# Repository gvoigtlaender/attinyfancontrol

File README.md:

# attinyfancontrol
control USB fan with Attiny85 &amp; DS18B20 Sensor

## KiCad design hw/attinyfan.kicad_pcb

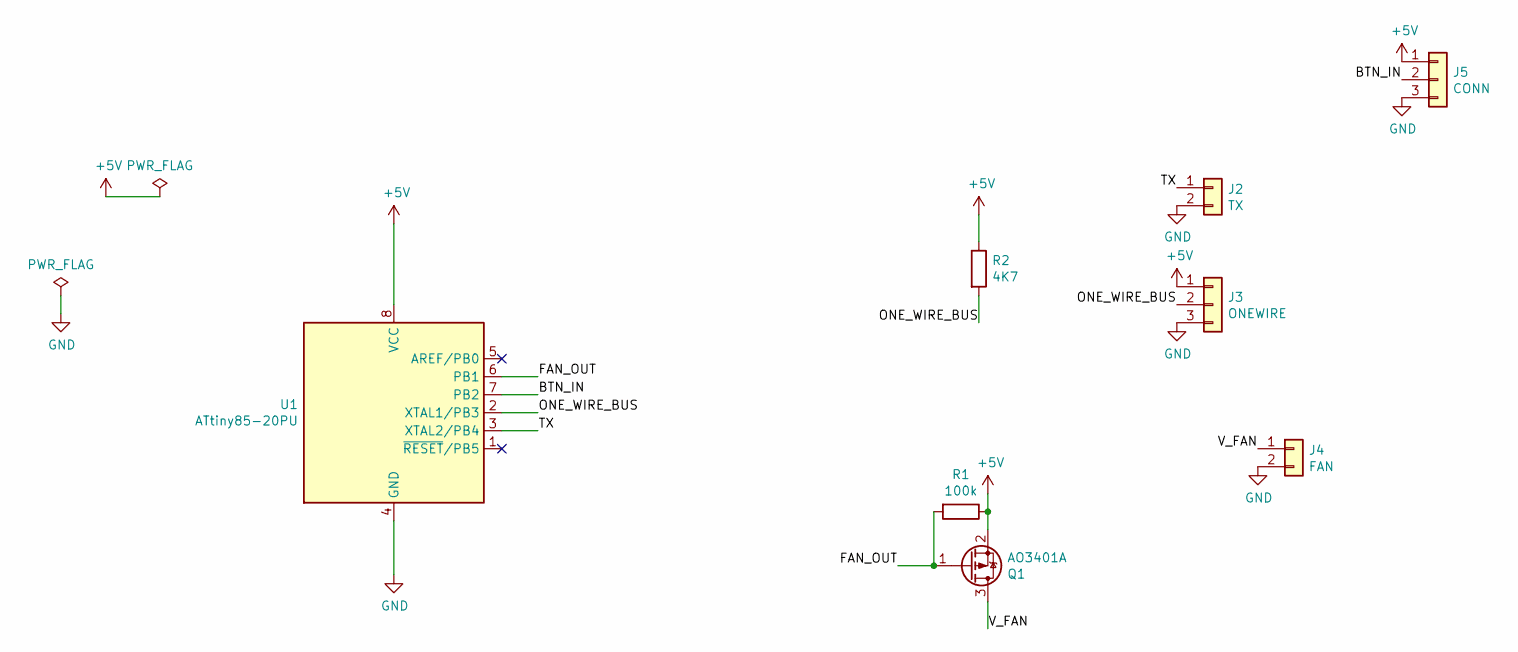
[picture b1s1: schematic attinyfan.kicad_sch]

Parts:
J2: TX; PinHeader_1x02_P2.54mm_Vertical
J3: ONEWIRE; PinHeader_1x03_P2.54mm_Vertical
J4: FAN; PinHeader_1x02_P2.54mm_Vertical
J5: CONN; PinHeader_1x03_P2.54mm_Vertical
Q1: AO3401A; SOT-23
R1: 100k; R_0805_2012Metric
R2: 4K7; R_0805_2012Metric
U1: ATtiny85-20PU; DIP-8_W7.62mm

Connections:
+5V: J3.1, J5.1, Q1.2 (S), R1.1, R2.1, U1.8 (VCC)
/BTN_IN: J5.2, U1.7 (PB2)
/FAN_OUT: Q1.1 (G), R1.2, U1.6 (PB1)
/ONE_WIRE_BUS: J3.2, R2.2, U1.2 (XTAL1/PB3)
/TX: J2.1, U1.3 (XTAL2/PB4)
/V_FAN: J4.1, Q1.3 (D)
GND: J2.2, J3.3, J4.2, J5.3, U1.4 (GND)

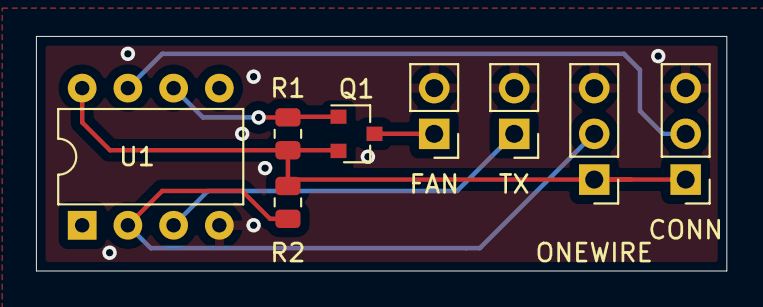
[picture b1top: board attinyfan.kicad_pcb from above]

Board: 2 copper layers, 38.4 x 13.0 mm, 8 parts (0 on the bottom side), 7 nets.

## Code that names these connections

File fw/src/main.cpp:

#include <Arduino.h>
#if defined USE_SOFTWARE_SERIAL
#include <SoftwareSerial.h>
#endif

#include <EEPROM.h>

#define FAN_OUT PB1
#define ONE_WIRE_BUS PB3
#define RX -1  // *** D3, Pin 2
#define TX PB4 // *** D4, Pin 3
#define BTN_IN PB2

#define USE_DS18B20_AVR

#define DEG                                                                    \
  "\xa7"                                                                       \
  "C"

#if defined USE_DS18B20_AVR
#include <bitop.h>
#include <ds18b20/ds18b20.h>
#endif

#if defined USE_SOFTWARE_SERIAL
SoftwareSerial _Serial(RX, TX);
#endif // USE_SOFTWARE_SERIAL

int16_t nTempTarget = 240;

bool bOn = false;
void setup() {
  // put your setup code here, to run once:
  delay(100);

#if defined USE_SOFTWARE_SERIAL
  _Serial.begin(57600);
  _Serial.println("Initializing...");
#endif // USE_SOFTWARE_SERIAL

  pinMode(FAN_OUT, OUTPUT);
  digitalWrite(FAN_OUT, !bOn);

  pinMode(BTN_IN, INPUT_PULLUP);

#if defined USE_DS18B20_AVR
  // set precision
  ds18b20wsp(&PORTB, &DDRB, &PINB, BIT(ONE_WIRE_BUS), NULL, 0, 0,
             DS18B20_RES12);
  ds18b20convert(&PORTB, &DDRB, &PINB, BIT(ONE_WIRE_BUS), NULL);
#endif

  EEPROM.begin();
  nTempTarget = EEPROM.get(0, nTempTarget);
  _Serial.print("nTT=");
  _Serial.println(nTempTarget);
}

void loop() {
  // put your main code here, to run repeatedly:
  delay(100);

  // static int8_t temp = 0;
  static int16_t temp16 = 0;
  bool bLog = false;
#if defined USE_DS18B20_AVR
  int16_t ntemp;
  static int16_t ntempprev = -1;
  if (DS18B20_ERROR_OK !=
      ds18b20read(&PORTB, &DDRB, &PINB, BIT(ONE_WIRE_BUS), NULL, &ntemp))
    ntemp = 1600;
  ds18b20convert(&PORTB, &DDRB, &PINB, BIT(ONE_WIRE_BUS), NULL);

  if (ntempprev != ntemp) {
    ntempprev = ntemp;
    float temperatur = ntemp / 16.0;
    // temp = temperatur;
    // char ctemp = (temperatur - temp) * 100;
    // _Serial.printf("%+0.2hd.%02d" DEG "\n", temp, ctemp);
    temp16 = ntemp / 1.6;
    // _Serial.print("temp16=");
    // _Serial.println(temp16);
    bLog = true;
  }
#endif

  if (bOn == false && temp16 >= (nTempTarget + 10)) {
    bOn = true;
    digitalWrite(FAN_OUT, !bOn);
#if defined USE_SOFTWARE_SERIAL
    // _Serial.println("FAN ON");
    bLog = true;
#endif // USE_SOFTWARE_SERIAL
  } else if (bOn == true && temp16 <= (nTempTarget - 10)) {
    bOn = false;
    digitalWrite(FAN_OUT, !bOn);
#if defined USE_SOFTWARE_SERIAL
    // _Serial.println("FAN OFF");
    bLog = true;
#endif // USE_SOFTWARE_SERIAL
  }

  static bool bBtn = false;

  if (bBtn == false && !digitalRead(BTN_IN)) {
    bBtn = true;
    // _Serial.println("BTN ON");
    bLog = true;
  } else if (bBtn == true && digitalRead(BTN_IN)) {
    bBtn = false;
    // bLog = true;_Serial.println("BTN OFF");
    nTempTarget = temp16;
    EEPROM.put(0, nTempTarget);
    _Serial.printf("nTT:=");
    _Serial.println(nTempTarget);
  }

  if (bLog) {
    _Serial.print("Tmp=");
    _Serial.print(temp16);
    _Serial.print(", [");
    _Serial.print(nTempTarget - 10);
    _Serial.print(":");
    _Serial.print(nTempTarget + 10);
    _Serial.printf("][B=%c][F=%c]\n", (bBtn ? 'X' : '0'), (bOn ? 'X' : '0'));
  }
}
